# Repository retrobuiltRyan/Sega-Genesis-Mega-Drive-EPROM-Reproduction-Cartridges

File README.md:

# Sega-Genesis-Mega-Drive-EPROM-Reproduction-Cartridges
https://youtu.be/jw_2mUTdxVY

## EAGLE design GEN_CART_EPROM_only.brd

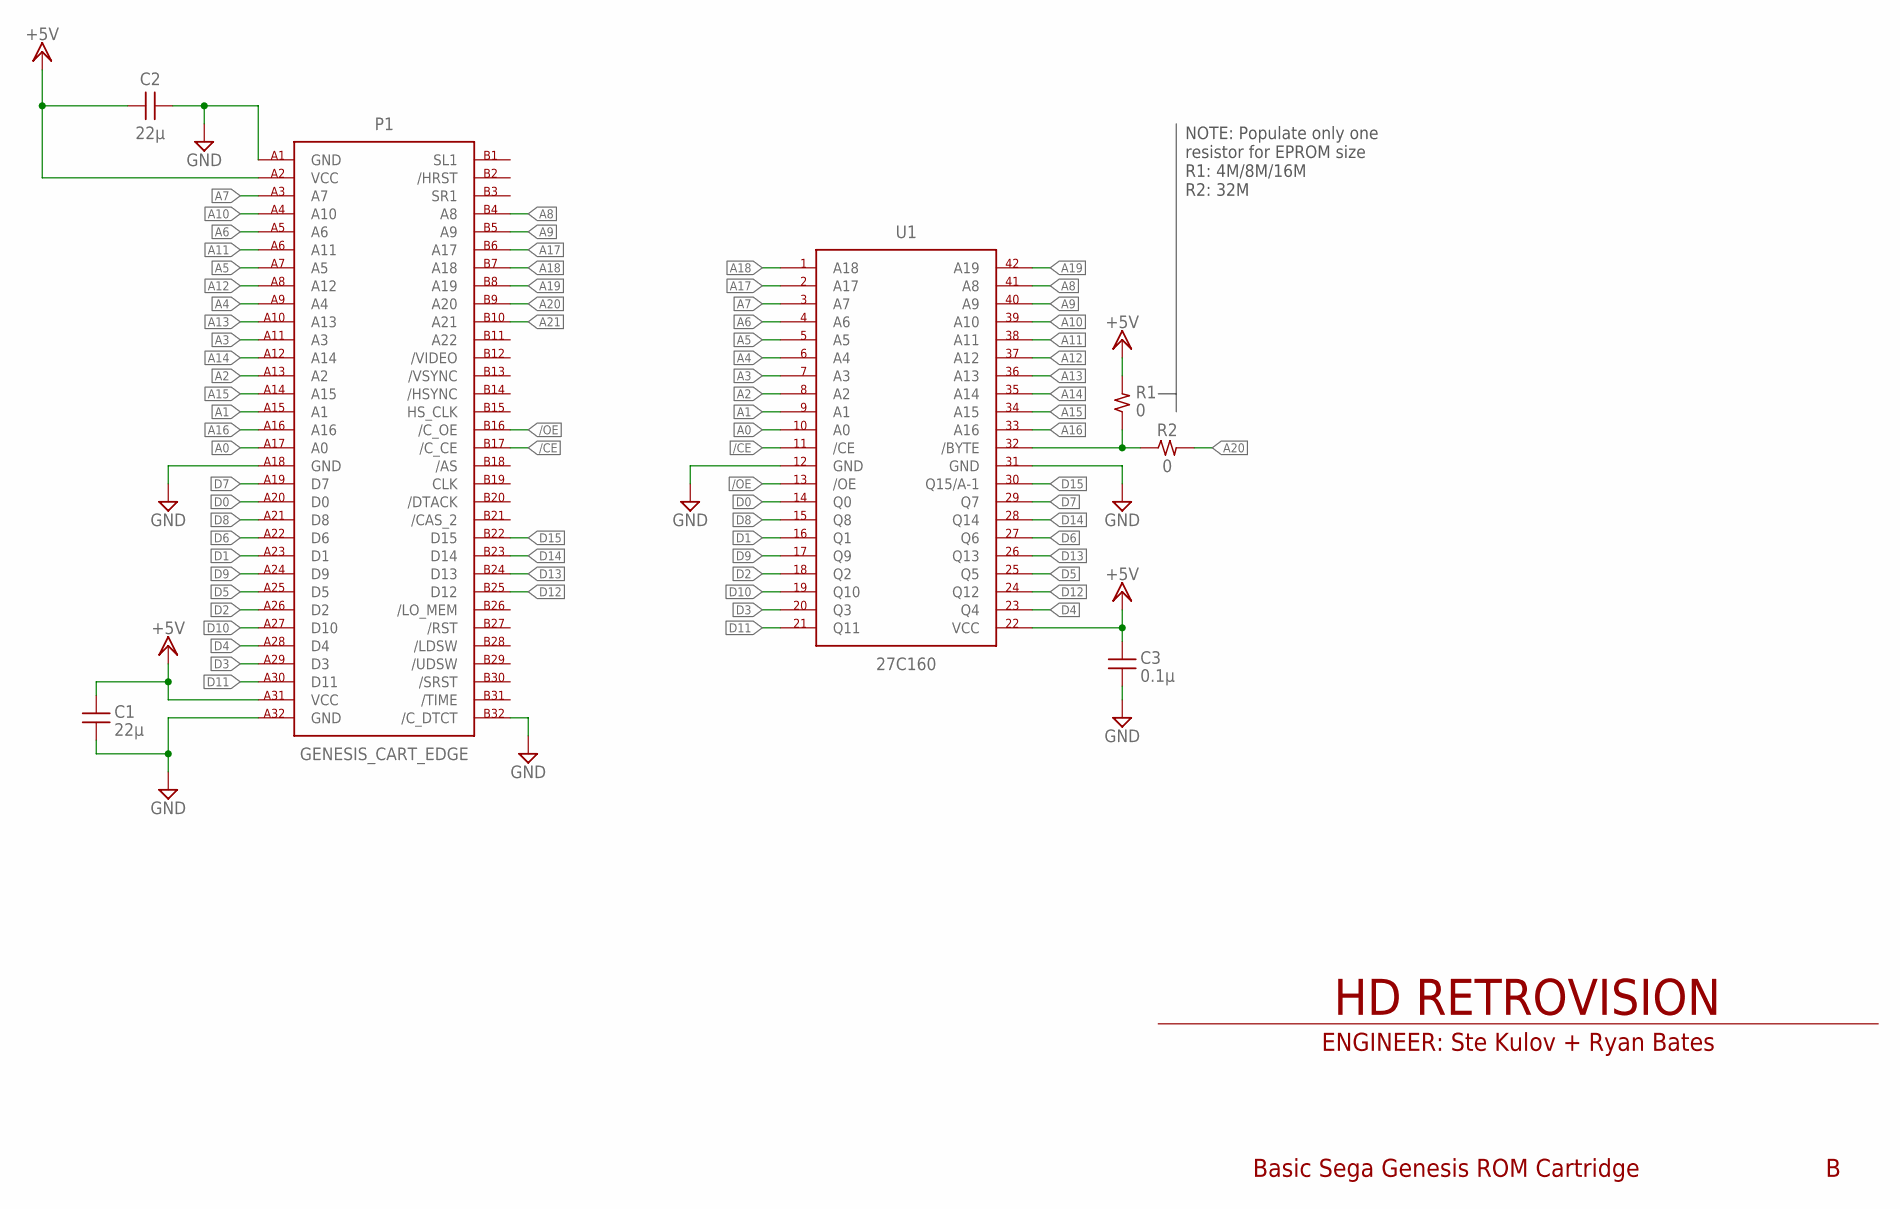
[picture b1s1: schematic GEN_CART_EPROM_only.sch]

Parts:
C1, C2: 22µ; CAP_SMD1210
C3: 0.1µ; CAP_SMD1210
P1: GENESIS_CART_EDGE
R1, R2: 0; RES_SMD0603
U1: 27C160; DIP_600MIL_42

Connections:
/CE: P1.B17 (/C_CE), U1.P$11 (/CE)
/OE: P1.B16 (/C_OE), U1.P$13 (/OE)
A0: P1.A17 (A0), U1.P$10 (A0)
A1: P1.A15 (A1), U1.P$9 (A1)
A2: P1.A13 (A2), U1.P$8 (A2)
A3: P1.A11 (A3), U1.P$7 (A3)
A4: P1.A9 (A4), U1.P$6 (A4)
A5: P1.A7 (A5), U1.P$5 (A5)
A6: P1.A5 (A6), U1.P$4 (A6)
A7: P1.A3 (A7), U1.P$3 (A7)
A8: P1.B4 (A8), U1.P$41 (A8)
A9: P1.B5 (A9), U1.P$40 (A9)
A10: P1.A4 (A10), U1.P$39 (A10)
A11: P1.A6 (A11), U1.P$38 (A11)
A12: P1.A8 (A12), U1.P$37 (A12)
A13: P1.A10 (A13), U1.P$36 (A13)
A14: P1.A12 (A14), U1.P$35 (A14)
A15: P1.A14 (A15), U1.P$34 (A15)
A16: P1.A16, U1.P$33 (A16)
A17: P1.B6 (A17), U1.P$2 (A17)
A18: P1.B7 (A18), U1.P$1 (A18)
A19: P1.B8 (A19), U1.P$42 (A19)
A20: P1.B9 (A20), R2.P$2 (2)
A21: P1.B10 (A21)
D0: P1.A20 (D0), U1.P$14 (Q0)
D1: P1.A23 (D1), U1.P$16 (Q1)
D2: P1.A26 (D2), U1.P$18 (Q2)
D3: P1.A29 (D3), U1.P$20 (Q3)
D4: P1.A28 (D4), U1.P$23 (Q4)
D5: P1.A25 (D5), U1.P$25 (Q5)
D6: P1.A22 (D6), U1.P$27 (Q6)
D7: P1.A19 (D7), U1.P$29 (Q7)
D8: P1.A21 (D8), U1.P$15 (Q8)
D9: P1.A24 (D9), U1.P$17 (Q9)
D10: P1.A27 (D10), U1.P$19 (Q10)
D11: P1.A30 (D11), U1.P$21 (Q11)
D12: P1.B25 (D12), U1.P$24 (Q12)
D13: P1.B24 (D13), U1.P$26 (Q13)
D14: P1.B23 (D14), U1.P$28 (Q14)
D15: P1.B22 (D15), U1.P$30 (Q15/A-1)
GND: C1.P$1, C2.P$1, C3.P$1, P1.A1 (GND), P1.A18 (GND), P1.A32 (GND), P1.B32 (/C_DTCT), U1.P$12 (GND), U1.P$31 (GND)
unnamed: R1.P$1 (1), R2.P$1 (1), U1.P$32 (/BYTE)
V+: C1.P$2, C2.P$2, C3.P$2, P1.A2 (VCC), P1.A31 (VCC), R1.P$2 (2), U1.P$22 (VCC)

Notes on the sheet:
HD RETROVISION
Basic Sega Genesis ROM Cartridge
ENGINEER: Ste Kulov + Ryan Bates
NOTE: Populate only one resistor for EPROM size R1: 4M/8M/16M R2: 32M

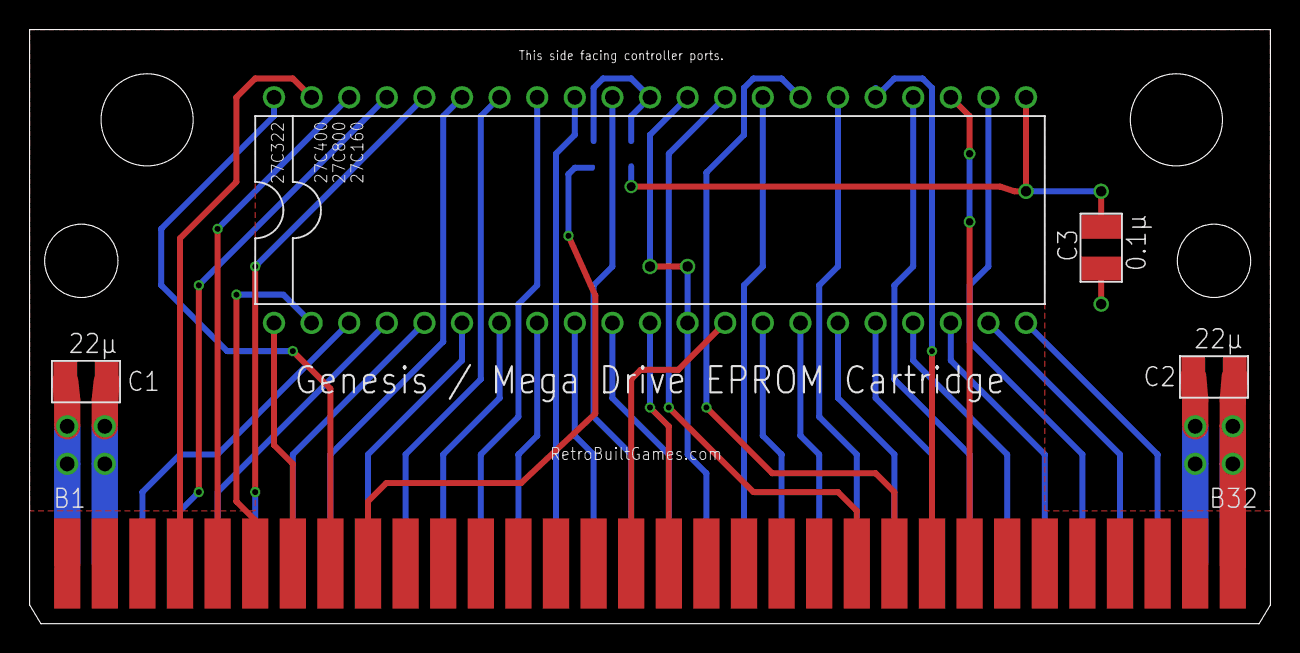
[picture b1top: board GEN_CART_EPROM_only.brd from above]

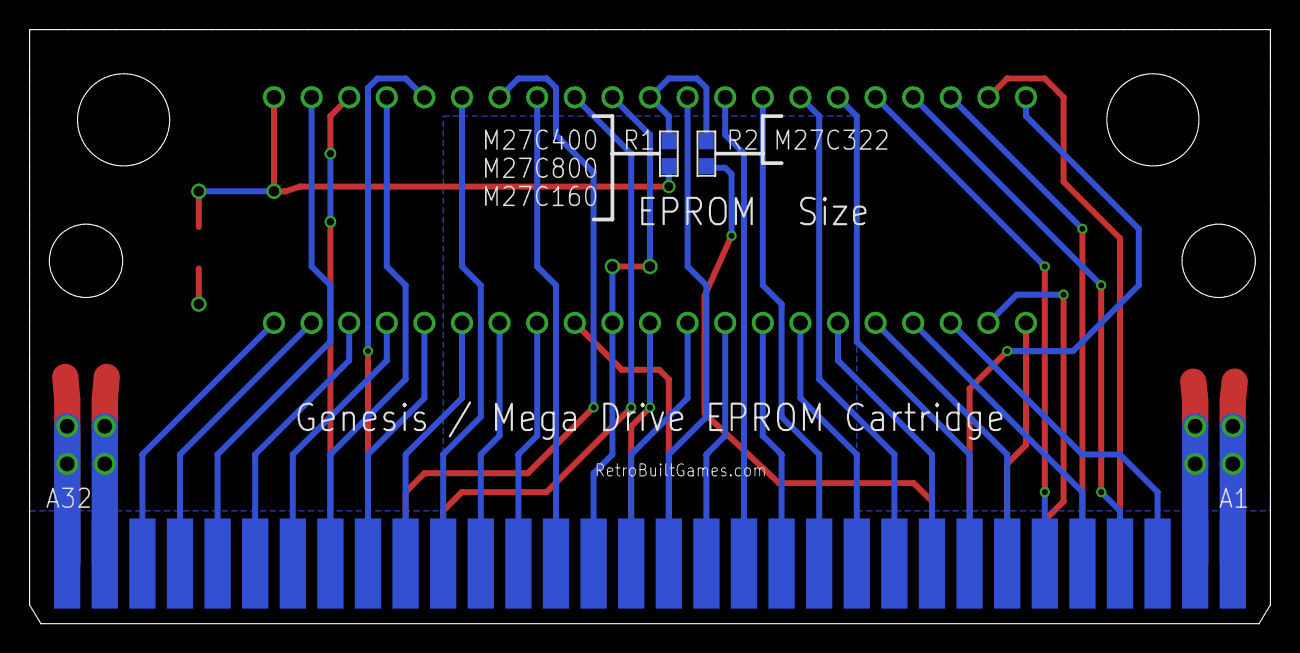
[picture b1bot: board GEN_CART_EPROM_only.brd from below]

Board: 2 copper layers, 83.8 x 40.1 mm, 7 parts (2 on the bottom side), 42 nets.
